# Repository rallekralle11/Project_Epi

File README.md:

# Epi
# This thing is about to get launched on Crowd Supply!
Also take a look at the better 4-layered version: https://github.com/rallekralle11/Epi_4L

Named after the Epipactis genus or orchids. The flower of one appears on the board.

With such "amazing" features as:

Data line ESD protection taken from the official A. micro.

Crenellated pins.

No integrated voltage converter, only runs at 4,5-5,5v(down to 2,7 if you make it with an 8mhz crystal, or use the internal oscillator).

USB-C connector sunk into the board, and slighly portruding from the end for panel mounting.

1,27mm pin spacing.

Extra pins broken out.

Way too many hours routing for my sanity, and i doubt it's optimal(i am a beginner).

Holes where M2 bolts can be used to hold it in place.

No rx/tx/power LEDs. Only one on pin 13 for testing.

Includes some custom footprints with 3D models.

Size comparisons.

Licensed under CERN-OHL-P v2

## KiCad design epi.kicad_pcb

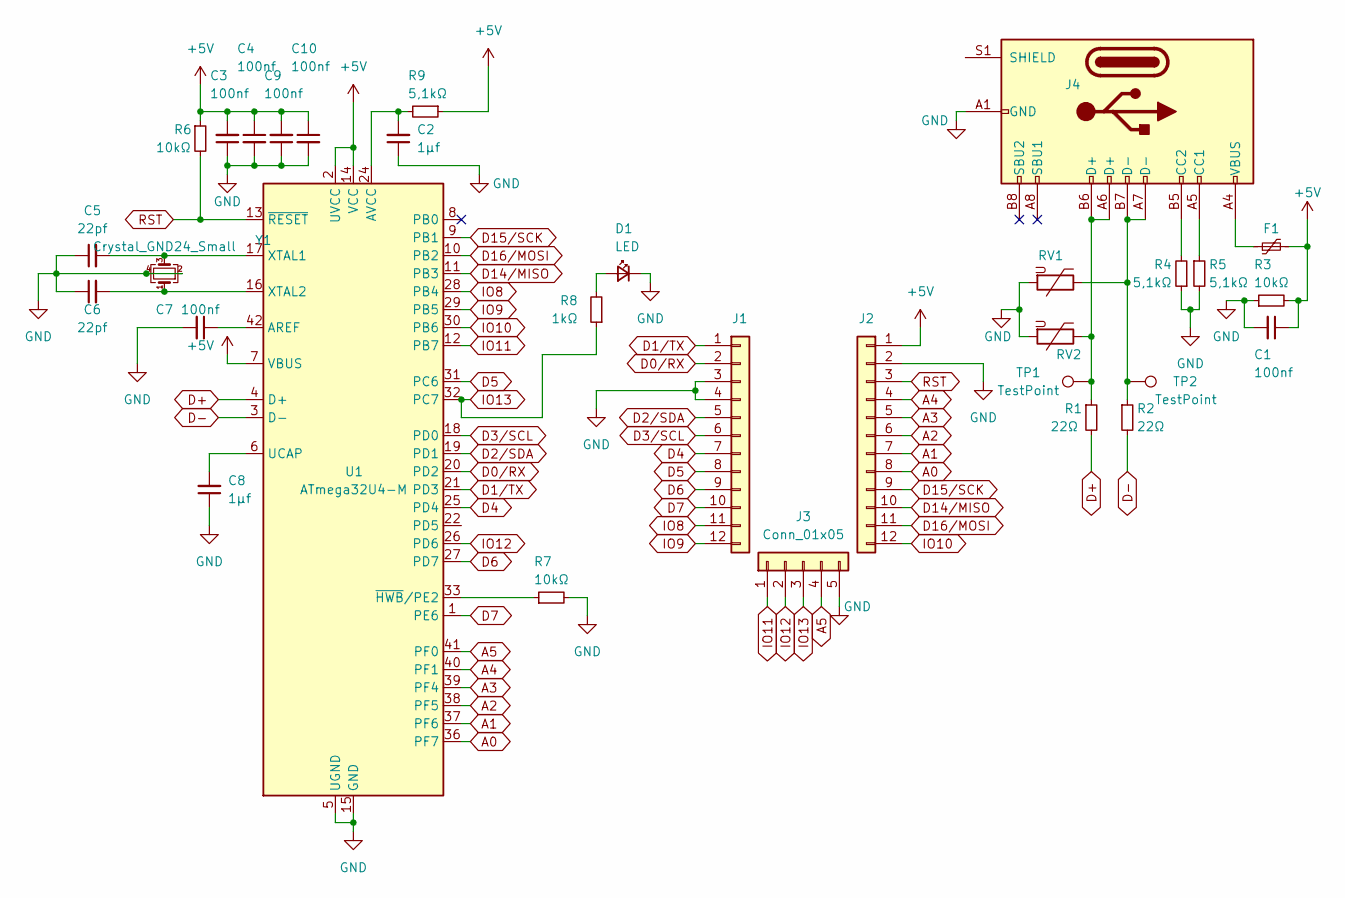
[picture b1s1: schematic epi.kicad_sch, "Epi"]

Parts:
C1, C3, C4, C7, C9, C10: 100nf; C_0402_1005Metric
C2, C8: 1µf; C_0402_1005Metric
C5, C6: 22pf; C_0402_1005Metric
D1: LED; LED_0402_1005Metric
F1: Polyfuse 500mA HC; Fuse_0402_1005Metric
J1, J2: Connector 1x12; PinHeader_1x12_P1.27mm_Vertical
J3: Conn_01x05; PinHeader_1x05_P1.27mm_Vertical
J4: USB-C 2.0 mid-mount female connector; USB-C MC-314C-4P16
R1, R2: 22Ω; R_0402_1005Metric
R3, R6, R7: 10kΩ; R_0402_1005Metric
R4, R5, R9: 5,1kΩ; R_0402_1005Metric
R8: 1kΩ; R_0402_1005Metric
RV1, RV2: ESD protection varistor; R_0402_1005Metric
TP1, TP2: TestPoint; TestPoint_Pad_D1.0mm
U1: ATmega32U4-M; QFN-44-1EP_7x7mm_P0.5mm_EP5.2x5.2mm
Y1: Crystal_GND24_Small; Crystal_SMD_2016-4Pin_2.0x1.6mm

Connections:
+5V: C1.1, C3.2, C4.1, C9.2, C10.1, F1.2, J2.1, R3.2, R6.1, R9.1, U1.2 (UVCC), U1.7 (VBUS), U1.14 (VCC), U1.34 (VCC)
A0: J2.8, U1.36 (PF7)
A1: J2.7, U1.37 (PF6)
A2: J2.6, U1.38 (PF5)
A3: J2.5, U1.39 (PF4)
A4: J2.4, U1.40 (PF1)
A5: J3.4, U1.41 (PF0)
D0/RX: J1.2, U1.20 (PD2)
D1/TX: J1.1, U1.21 (PD3)
D2/SDA: J1.5, U1.19 (PD1)
D3/SCL: J1.6, U1.18 (PD0)
D4: J1.7, U1.25 (PD4)
D5: J1.8, U1.31 (PC6)
D6: J1.9, U1.27 (PD7)
D7: J1.10, U1.1 (PE6)
D14/MISO: J2.10, U1.11 (PB3)
D15/SCK: J2.9, U1.9 (PB1)
D16/MOSI: J2.11, U1.10 (PB2)
D+: R1.2, U1.4 (D+)
D-: R2.2, U1.3 (D-)
GND: C1.2, C2.1, C3.1, C4.2, C5.1, C6.1, C7.2, C8.1, C9.1, C10.2, D1.1 (K), J1.3, J1.4, J2.2, J3.5, J4.A1 (GND), J4.A12 (GND), J4.B1 (GND), J4.B12 (GND), R3.1, R4.1, R5.2, R7.2, RV1.2, RV2.2, U1.5 (UGND), U1.15 (GND), U1.23 (GND), U1.35 (GND), U1.43 (GND), U1.45 (GND), Y1.2, Y1.4
IO8: J1.11, U1.28 (PB4)
IO9: J1.12, U1.29 (PB5)
IO10: J2.12, U1.30 (PB6)
IO11: J3.1, U1.12 (PB7)
IO12: J3.2, U1.26 (PD6)
IO13: J3.3, R8.1, U1.32 (PC7)
unnamed: C2.2, R9.2, U1.24 (AVCC), U1.44 (AVCC)
unnamed: C5.2, U1.17 (XTAL1), Y1.3
unnamed: C6.2, U1.16 (XTAL2), Y1.1
unnamed: C7.1, U1.42 (AREF)
unnamed: C8.2, U1.6 (UCAP)
unnamed: D1.2 (A), R8.2
unnamed: F1.1, J4.A4 (VBUS), J4.A9 (VBUS), J4.B4 (VBUS), J4.B9 (VBUS)
unnamed: J4.A5 (CC1), R5.1
unnamed: J4.A6 (D+), J4.B6 (D+), R1.1, RV2.1, TP1.1
unnamed: J4.A7 (D-), J4.B7 (D-), R2.1, RV1.1, TP2.1
unnamed: J4.B5 (CC2), R4.2
unnamed: R7.1, U1.33 (~HWB/PE2)
RST: J2.3, R6.2, U1.13 (~RESET)

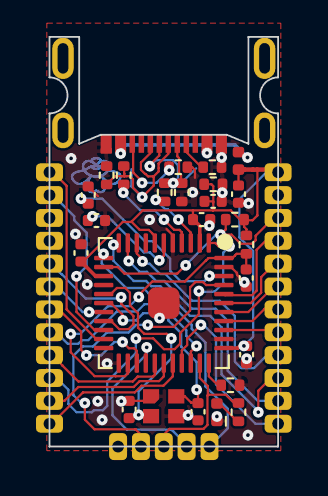
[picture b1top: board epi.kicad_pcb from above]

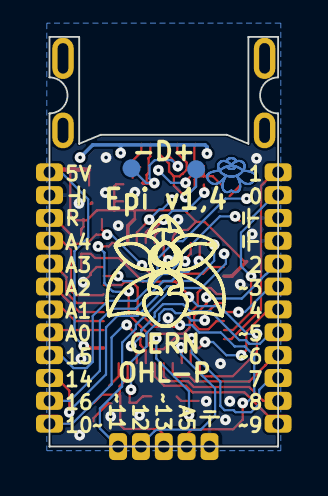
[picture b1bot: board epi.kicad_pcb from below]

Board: 2 copper layers, 12.7 x 22.8 mm, 31 parts (2 on the bottom side), 40 nets.

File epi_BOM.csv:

"Id";"Designator";"Package";"Quantity";"Designation";"Supplier and ref"
1;"C8,C2";"C_0402_1005Metric";2;"1µf";;;
2;"RV1,RV2";"R_0402_1005Metric";2;"Varistor";;;
3;"R4,R5";"R_0402_1005Metric";2;"56kΩ";;;
4;"C1,C7";"C_0402_1005Metric";2;"100nf";;;
5;"U1";"QFN-44-1EP_7x7mm_P0.5mm_EP5.2x5.2mm";1;"ATmega32U4-M";;;
6;"D2";"LED_0402_1005Metric";1;"LED_Small";;;
7;"R2,R1";"R_0402_1005Metric";2;"22Ω";;;
8;"R6,R7,R3";"R_0402_1005Metric";3;"10kΩ";;;
9;"J3";"PinHeader_1x04_P1.27mm_Vertical";1;"Conn_01x04";;;
10;"FB1";"R_0402_1005Metric";1;"MH2029-300Y";;;
11;"D1";"D_0402_1005Metric";1;"D_Small";;;
12;"C6,C4,C3,C5";"C_0402_1005Metric";4;"22pf";;;
13;"J1,J2";"PinHeader_1x12_P1.27mm_Vertical";2;"Conn_01x12";;;
14;"Y1";"Crystal_SMD_2016-4Pin_2.0x1.6mm";1;"16mhz";;;
15;"R8";"R_0402_1005Metric";1;"1kΩ";;;
16;"J4";"USB-C MC-314C-4P16";1;"USB_C_Receptacle_USB2.0";;;
17;"F1";"Fuse_0402_1005Metric";1;"Polyfuse_500mA";;;

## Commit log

2022-10-29 adding everything
2022-10-29 board updates and readme
2022-10-29 bit of everything
2022-10-29 finished routing main pins
2022-10-30 finished routing and more
2022-10-30 added better picture
2022-10-30 changed 3D models and updated picture
2022-10-30 bit of everything and name change
2022-10-30 small trace fix
2022-10-30 added comparison picture
2022-10-30 mixed changes
2022-10-31 slight redesign
2022-10-31 pictures and readme
2022-10-31 comparison pic ++
2022-10-31 mostly readme
2022-11-01 experimental production files update++
2022-11-03 redesign, added fuse
2022-11-03 updated gerbers and removed misplaced folder
2022-11-03 readme and picture fix
2022-11-03 fiddling with pictures 1
2022-11-03 fiddling with pictures 2
2022-11-04 fixed small USB port inaccuracy
2022-11-04 updated BOM
2022-11-04 more descriptive part names and better BOM
2022-11-05 increased trace spacing and a few other changes
2022-11-08 bit of this and bit of that
2022-11-08 updaated gerbers
2022-11-15 fixed some dumb missed connection
2022-11-15 removed unused files
2022-11-25 updated pictures
2022-12-07 recommit
2022-12-08 fixed a wrong pin number
2022-12-14 updated picture
2023-01-04 initial
2023-01-04 fail
2023-01-04 messed up and reuploaded it all
